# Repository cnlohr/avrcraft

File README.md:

# avrcraft (For Minecraft 1.11)

Minecraft server optimized for 8-bit devices.

Check out the AVR version of this in this video:
http://www.youtube.com/watch?v=EZRLOanNQ_w

This has a few subprojects.
* dumbcraft => Minimalistic Core C Minecraft Server
+ demo_x86_dumbcraft => dumbcraft wrapper for Linux desktops
+ demo_mineandhttp => dumbcraft wrapper for atmega328
* http => http server and demo
* avr_hardware => board layout design for AVR server
* ipcore => core AVR IP stack for the enc424j600 (Though has been ported to a wide variety of targets)
* mfs => minimalistic read-only in-flash filesystem for AVRs
* microsd => minimalistic FAT32 read-only SD/SDHC filesystem for AVRs
* ntsc => Code to help produce text-mode NTSC.

+indicates available tests.

## Installing Minecraft 11.1

Install JDK 8

`sudo apt-get install openjdk-8-jre`

Download the official Minecraft Launcher.

Click "Minecraft: Java Edition"
Click the "Installations" tab.
Create a new installation.
Select Minecraft 1.11 from the list.
Under more settings, select `/usr/lib/jvm/java-8-openjdk-amd64/bin/java`

Launch!

## LICENSE
All code in this repository that was authored by me is freely licensable under the MIT/x11 or NewBSD licenses.

## Original README (For running on 8-bit AVRs)

My 8-bit Microscope Slide Minecraft Server

All contents is Copyright 2012 <>< Charles Lohr
All code and documentation is licensed under the MIT-x11 or NewBSD license.
You choose.  See license info at the end of this readme.
You can use this minecraft server and associated TCP/IP stack commercially.

Check out the AVR version of this in this video:
http://www.youtube.com/watch?v=EZRLOanNQ_w

This has a few subprojects.
* dumbcraft => Minimalistic Core C Minecraft Server
+ demo_x86_dumbcraft => dumbcraft wrapper for Linux desktops
+ demo_mineandhttp => dumbcraft wrapper for atmega328
* http => http server and demo
* avr_hardware => board layout design for AVR server
* ipcore => core AVR IP stack for the enc424j600
* mfs => minimalistic read-only in-flash filesystem for AVRs
* microsd => minimalistic FAT32 read-only SD/SDHC filesystem for AVRs
* ntsc => Code to help produce text-mode NTSC.
+indicates available tests.

----Overview----

This is my 8-bit AVR Minecraft Server... and some extra goodies.  This package
includes:

  * 754lib - A toolset for IEEE754-1985 doubles and floats to fixed point
  * os_generic - My toolset threads (unused), mutices (unused), and timing
  * util10 - My integer->string toolset for this project.
  * dumbcraft (.c, .h)
  * an x86 demo for dumbcraft (compiles and runs on Linux)
  * an AVR-buildable copy (see below)
  * a tool for generating gzipped map chunks (requires Linux)

The AVR folder contains:

  * avr_print - SPI debugging toolset (for use with tinyisp and tinyispterm)
  * my bitbanged ethernet (MAC + ARP + ICMP + UDP + TCP) driver (see below)
  * a really dumb HTTP server
  * a driver for SD cards (and a FAT32 driver) NO SUPPORT FOR FAT16!

Oh yeah, with debugging on, this all fits in about 17kB.

Depending on your settings (dumbcraft circular buffer, etc.) you can use
from about 600 bytes of static RAM to about 1.5 comfortably.

Sadly this does not include the stack, so if you can push data to the
clients and forget about it, that's probably for the best.

----What the dumbcraft does (and doesn't do)----

Dumbcraft is split into a C file for the core, and a user C file that contains
various action-related functions that you must support, i.e.:
  * void InitDumbgame()
  * void DoCustomPreloadStep( uint8_t playerid )
  * void PlayerTickUpdate( int playerid )
  * void PlayerClick( uint8_t playerid, uint8_t x, uint8_t y, uint8_t z )
  * void PlayerUpdate( uint8_t playerid )
  * uint8_t ClientHandleChat( char * chat, uint8_t chatlen )

The .C file contains the core dumbcraft toolset.  Because it doesn't support
any mode of communications with the outside world, all communications must be
done through various functions.  These functions interface 

What works:
  * The stock Minecraft 1.4.2 Server on Windows or Linux (most of the time)
  * More than one player
  * Running around
  * Pulling Levers
  * Updating blocks
  * Loading main map chunk
  * Chat

What doesn't work:
  * Day/night
  * MOBs
  * Physics
  * Animations
  * Crafting
  * Falling Blocks
  * Mining
  * Placing Blocks
  * Collecting things
  * The Nether
  * The End
  * Redstone
  * Water
  * Lava
  * Well, just about everything.

Take a look through dumbcraft.c to get a better hint as to how this all goes together.

----Mapmake----

Map make creates a chunk to be sent by 0x33.  This code doesn't seem to work
very well... It seems to work well enough to make big plot of green ground.

Try dinking with this to figure out why some other chunk types don't work?

It's used to generate the 'mapdata' buffer used in dumbcraft.c

----My IP Stack----

I wrote my own TCP/IP stack for this project, I've been working with it for
quite some time and I needed a good test.  Minecraft has shown to be an
excellent test.  It uses an ENC424j600 from Microchip in SPI mode. It doesn't
use the SPI hardware on an AVR, instead it bit bangs all communications with
it.  This is to make it possible to put it on any geographically convenient
pins.  (I do this on one-layer)

The stack contains the main MAC code and a file for the low level SPI
functionality.  Since the SPI has to be really fast, I've opted to write it
in assembly.

If you want to use the TCP/IP stack, you can feel free to copy it all out,
including test.c and rip out my code.  You'll need the basic callbacks from
TCP or UDP, but other than that you're good to go.

Reconfigure eth_config.h to your situation and profit.  You can get a UDP
server in a little under 4kB, and TCP for an extra ~2.5k more.

I included an HTTP server with it, but it barely counts as an HTTP server
since it requires additional code to serve ... anything.  You can see that it
is difficult to get it to server webpages from the SD card :-/.

----My FAT32/SD SPI Stack----

This stack is still pretty buggy but lets you read files from a FAT32
partition on a SD card.  It can either bin the root or in the FIRST partition.

It can list files in a folder, seek to folders, open files and read them 
sequentially... that's... about... it. 

The SD driver supports SDHC and SD cards and supports reading/writing at the
block level.  Keep in mind the FAT32 driver does not support writing.

Consider the test.c in the avr folder an example of how to do this.

----Building----

You'll need at the minimum: avrdude, avr-gcc and basic build-utils. I
recommend you get my copy of tinyispterm since that'll help you debug.

It prints debugging data through the SPI port if -DMUTE_PRINTF isn't set.
Everything's geared around a TinyISP from LadyAda... I personally use a tiny
variant of it I designed.  You can get the single-layer designs and the tool
here:

https://github.com/cnlohr/tinyispterm

The hardware details for this project can be found in the avr_hardware folder.

I am not a trained electrical engineer.  You will have to know your stuff
before venturing on this project!  It is tricky, and I didn't really document
anything very well.

I designed the PCB in ExpressPCB and designed the schematic later.  They don't
match and I got frustrated, so trust the PCB over the SCH.

Yes, it's a single layer.  No, there are no jumpers.

----Resources and Thanks----

Special thanks to the folks at #mcdevs.  They made this awesome thing here:
http://www.wiki.vg/Protocol

Thanks to nickelpro at #mcdevs for helping me with 1.7 support.

I used a few guides when working on the SD card code.
http://www.esawdust.com/blog/serial/files/SPI_SD_MMC_ATMega128_AVR.html
http://elm-chan.org/docs/mmc/mmc_e.html 

For the FAT32 driver, I used this:
http://staff.washington.edu/dittrich/misc/fatgen103.pdf

----The MIT/x11 License----

Permission is hereby granted, free of charge, to any person obtaining a copy
of this software and associated documentation files (the "Software"), to deal
in the Software without restriction, including without limitation the rights
to use, copy, modify, merge, publish, distribute, sublicense, and/or sell
copies of the Software, and to permit persons to whom the Software is
furnished to do so, subject to the following conditions:

The above copyright notice and this permission notice shall be included in
all copies or substantial portions of the Software.

THE SOFTWARE IS PROVIDED "AS IS", WITHOUT WARRANTY OF ANY KIND, EXPRESS OR
IMPLIED, INCLUDING BUT NOT LIMITED TO THE WARRANTIES OF MERCHANTABILITY,
FITNESS FOR A PARTICULAR PURPOSE AND NONINFRINGEMENT. IN NO EVENT SHALL THE
AUTHORS OR COPYRIGHT HOLDERS BE LIABLE FOR ANY CLAIM, DAMAGES OR OTHER
LIABILITY, WHETHER IN AN ACTION OF CONTRACT, TORT OR OTHERWISE, ARISING FROM,
OUT OF OR IN CONNECTION WITH THE SOFTWARE OR THE USE OR OTHER DEALINGS IN THE
SOFTWARE.

----The NewBSD License----

Redistribution and use in source and binary forms, with or without
modification, are permitted provided that the following conditions are met:

    Redistributions of source code must retain the above copyright notice,
     this list of conditions and the following disclaimer.

    Redistributions in binary form must reproduce the above copyright notice,
     this list of conditions and the following disclaimer in the documentation
     and/or other materials provided with the distribution.

THIS SOFTWARE IS PROVIDED BY THE COPYRIGHT HOLDERS AND CONTRIBUTORS "AS IS"
AND ANY EXPRESS OR IMPLIED WARRANTIES, INCLUDING, BUT NOT LIMITED TO, THE
IMPLIED WARRANTIES OF MERCHANTABILITY AND FITNESS FOR A PARTICULAR PURPOSE
ARE DISCLAIMED. IN NO EVENT SHALL THE COPYRIGHT HOLDER OR CONTRIBUTORS BE
LIABLE FOR ANY DIRECT, INDIRECT, INCIDENTAL, SPECIAL, EXEMPLARY, OR
CONSEQUENTIAL DAMAGES (INCLUDING, BUT NOT LIMITED TO, PROCUREMENT OF
SUBSTITUTE GOODS OR SERVICES; LOSS OF USE, DATA, OR PROFITS; OR BUSINESS
INTERRUPTION) HOWEVER CAUSED AND ON ANY THEORY OF LIABILITY, WHETHER IN
CONTRACT, STRICT LIABILITY, OR TORT (INCLUDING NEGLIGENCE OR OTHERWISE)
ARISING IN ANY WAY OUT OF THE USE OF THIS SOFTWARE, EVEN IF ADVISED OF
THE POSSIBILITY OF SUCH DAMAGE.

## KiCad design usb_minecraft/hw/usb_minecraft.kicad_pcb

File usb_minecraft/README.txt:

THIS SUBPROJECT IS AWFUL.

DO NOT USE IT FOR ANYTHING.

IT IS NOT INTENDED AS A LEGITIMATE SOLUTION AND CRASHES ALL THE TIME.

There's a reason I called my modded TCP stack "tcp_awful."  It actually drops packets!

But, I did it, I shoehorned a full Minecraft server down to under 1k RAM, using a USB RNDIS Ethernet driver from LUFA.

IP is 192.168.55.243:25565... It totally works.

(Minecraft 1.8)

Boy it would be nice to know what's causing most of these errors!!

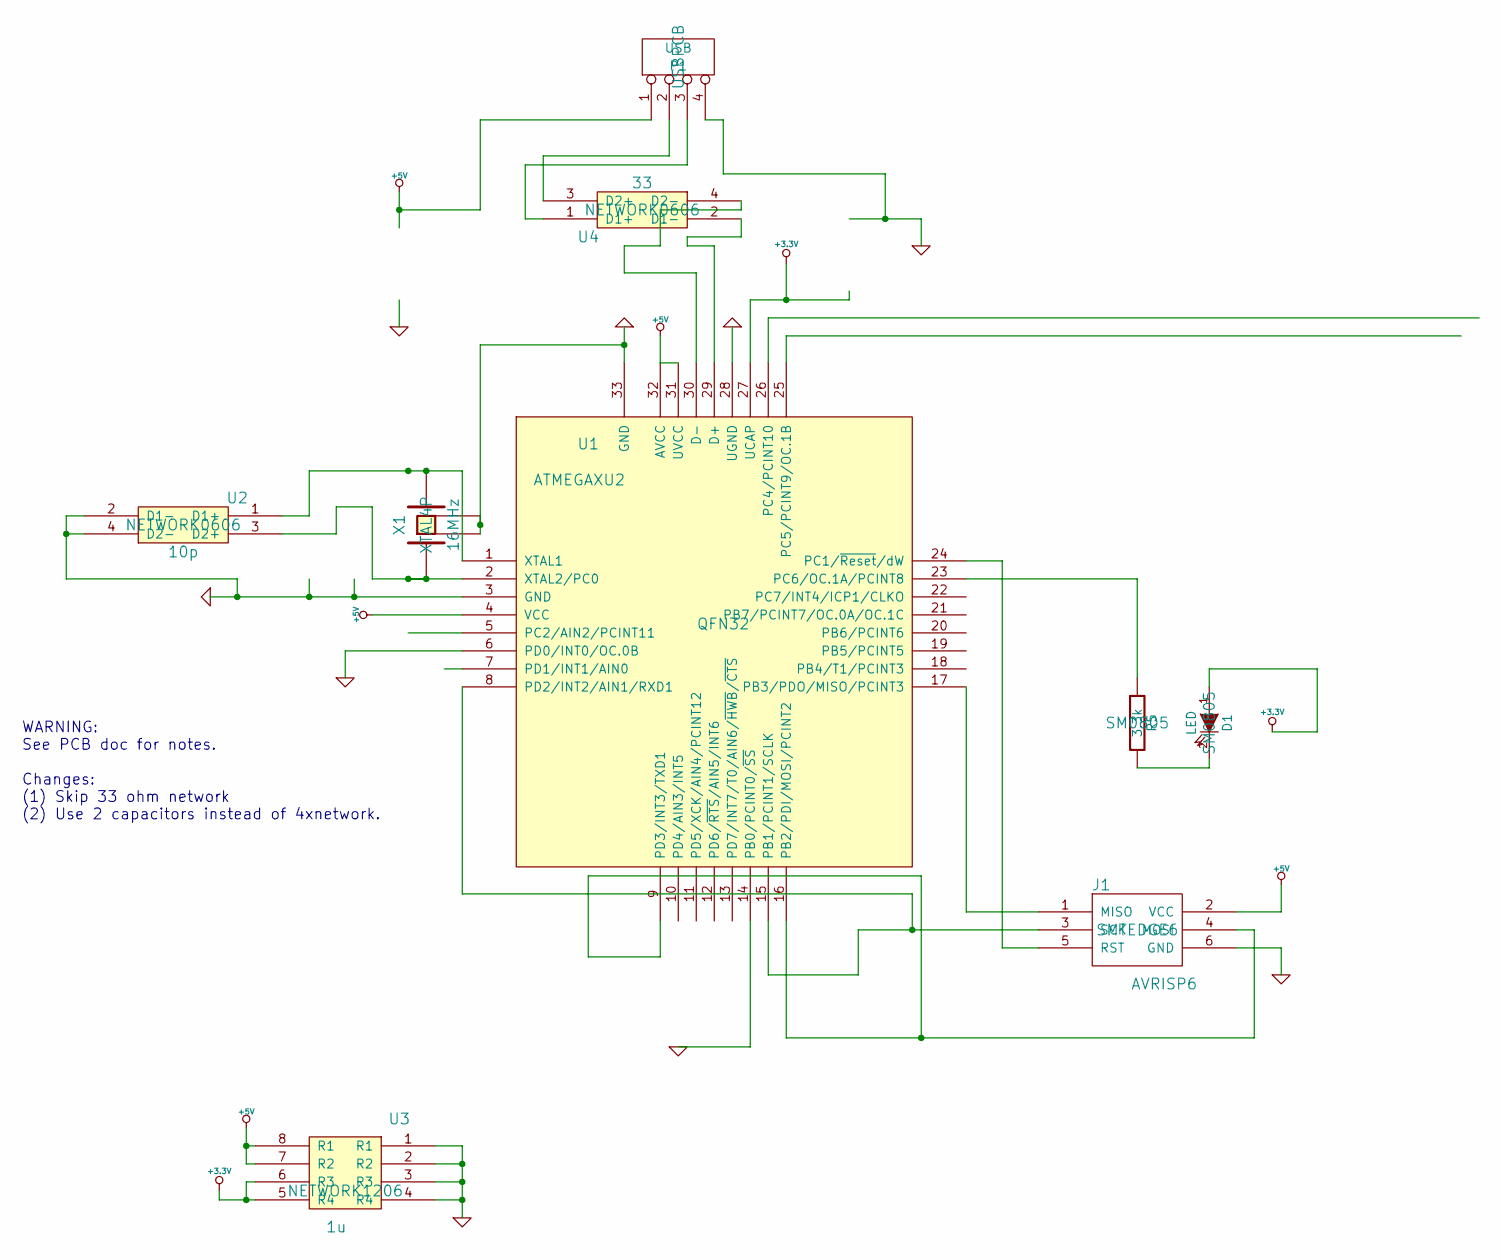
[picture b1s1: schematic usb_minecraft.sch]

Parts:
D1: LED; SM0805
J1: AVRISP6; SMTEDGE6
P1: USB; USBPCB
R5: 3.3k; SM0805
U1: ATMEGAXU2; QFN32
U2: 10p; NETWORK0606
U3: 1u; NETWORK1206
U4: 33; NETWORK0606
X1: 16MHz; XTAL4P

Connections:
+3.3V: D1.1 (A), U1.27 (UCAP), U3.5 (R4), U3.6 (R3)
+5V: J1.2 (VCC), P1.1, U1.4 (VCC), U1.31 (UVCC), U1.32 (AVCC), U3.7 (R2), U3.8 (R1)
GND: J1.6 (GND), P1.4, U1.3 (GND), U1.6 (PD0/INT0/OC.0B), U1.14 (PB0/PCINT0/~SS), U1.28 (UGND), U1.33 (GND), U2.2 (D1-), U2.4 (D2-), U3.1 (R1), U3.2 (R2), U3.3 (R3), U3.4 (R4), X1.3 (GND), X1.4 (GND)
unnamed: U1.29 (D+), U4.2 (D1-)
unnamed: U1.30 (D-), U4.4 (D2-)
unnamed: R5.1, U1.23 (PC6/OC.1A/PCINT8)
unnamed: J1.4 (MOSI), U1.9 (PD3/INT3/TXD1), U1.16 (PB2/PDI/MOSI/PCINT2)
unnamed: D1.2 (K), R5.2
unnamed: P1.2, U4.3 (D2+)
unnamed: P1.3, U4.1 (D1+)
unnamed: J1.3 (SCK), U1.8 (PD2/INT2/AIN1/RXD1), U1.15 (PB1/PCINT1/SCLK)
unnamed: J1.5 (RST), U1.24 (PC1/~Reset~/dW)
unnamed: J1.1 (MISO), U1.17 (PB3/PDO/MISO/PCINT3)
unnamed: U1.2 (XTAL2/PC0), U2.3 (D2+), X1.1
unnamed: U1.1 (XTAL1), U2.1 (D1+), X1.2

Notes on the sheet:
WARNING: See PCB doc for notes. Changes: (1) Skip 33 ohm network (2) Use 2 capacitors instead of 4xnetwork.

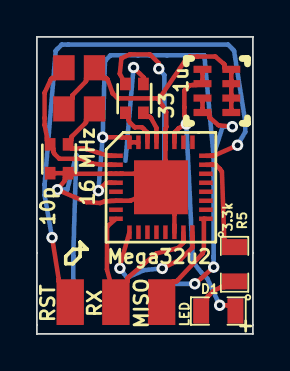
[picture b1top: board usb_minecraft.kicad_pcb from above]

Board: 2 copper layers, 12.0 x 16.5 mm, 9 parts (1 on the bottom side), 15 nets.

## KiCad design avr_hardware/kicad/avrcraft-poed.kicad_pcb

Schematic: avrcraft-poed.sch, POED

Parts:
C1: NP; SM0603
C4, C8: 10u; SM0805
C9: 100u; SM1206; Voltage 6.3v; Digikey 490-7217-1-ND
C12: .22u; SM0603
C13: .01u; SM0603
C15: 100u; PanasonicD8Cap
C16: 10u; SM0603
CN1, CN3: 10p; NETWORK0606
CN2, CN5: .1u; NETWORK0606
CN4: 10n; NETWORK1206
D1: 5050RGB
D3, D4: MB2S-TP; BESOP-4
D5: DIODESCH; DO_214AA
D7: ZENER-5.6V/2W; DO_214AA
H1, H2, H3, H4: ?; 632HOLE
J1: AVRISP6; RIBBON6SMT
L1: 68uH; BOURNS-SRR1280
P1: ETHERNET; SMT_ETHERNET
P2: ADC0; .1SMTPIN
P3: ADC1; .1SMTPIN
P4, P10: GND; .1SMTPIN
P5: 6MULTI; RIBBON6SMT
P6: 5V; .1SMTPIN
P7: 3V3; .1SMTPIN
P8: CONN_3X2; RIBBON6SMT
P9: 48V; .1SMTPIN
P11: +5V; .2SMTPIN
P12, P13: GND; .2SMTPIN
P14: +3.3V; .2SMTPIN
P15: POE+; .2SMTPIN
R1: 10; SM0805
R3: 12.4k; SM0603
R9, R11: 25k; SM0603
R13: 1k; SM0603
R15: 270k; SM0805
R16: NC; SM0805
RN1, RN4: 4.7k; NETWORK0606
RN2: 1k; NETWORK1206
RN3: 49.9; NETWORK1206
T1: S558-5999-T7-F; BELFuse-S553
U1: ATMEGA328; TQFP32
U2: MCP1824v3.3; SOT23-5
U3: ENC424J600; TQFP44
U4: A4447SLJTR; SO8E-WITHPAD
U5: S4SRP; DO-214AA
X1: 20MHz; XTAL4P
X2: 25MHz; XTAL4P

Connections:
+3.3V: C8.1, CN5.2, P5.4, P7.1, P14.1, R1.1, RN1.1, RN1.3, RN2.4, U2.5 (OUT), U3.4 (VDDosc), U3.12 (VDDpll), U3.15 (VDDrx), U3.18 (VDDtx), U3.44 (VDD)
+5V: C1.1, C9.1, C16.1, CN2.2, CN5.4, J1.2 (VCC), L1.1, P5.2, P6.1, P8.2, P11.1, RN4.2, U1.4 (VCC), U1.6 (VCC), U1.18 (AVCC), U2.1 (Vin), U2.3 (~SHDN), U4.6 (VIBAS)
/HighCOut: C13.1, D5.2 (K), L1.2, U4.7 (LXOUT)
/MISO: J1.1 (MISO), U1.16 ((PCINT4/MISO)PB4)
/MOSI: J1.4 (MOSI), U1.15 ((PCINT3/OC2A/MOSI)PB3), U1.19 (ADC6)
/PB0/CLKO: P8.1, U1.12 ((PCINT0/CLKO/ICP1)PB0)
/PB1/OC1A: P5.5, U1.13 ((PCINT1/OC1A)PB1)
/PD2/INT0: P8.3, U1.32 ((PCINT18/INT0)PD2)
/PD3/INT1/OC2B: P8.4, U1.1 ((PCINT19/OC2B/INT1)PD3)
/PD5/OC0B: P8.5, U1.9 ((PCINT21/OC0B/T1)PD5)
/POE+: D3.3 (+), D4.3 (+), D7.2 (K)
/POE+A: C12.2, C15.2, P9.1, P15.1, R16.2, U4.8 (VIN), U5.1
/POE+C: D7.1 (A), R15.1, U5.3
/POEA: D3.2 (AC), P1.7, P1.8, R11.1
/POEB: D3.1 (AC), P1.4, P1.5, R11.2
/POEC: D4.2 (AC), R9.2, T1.2 (PM)
/POED: D4.1 (AC), R9.1, T1.7 (PM)
/RST: J1.5 (RST), U1.29 ((PCINT14/RESET)PC6)
/SCK: J1.3 (SCK), U1.17 ((PCINT5/SCK)PB5), U1.22 (ADC7)
/SCL/PC5/PD7: P5.3, RN1.2, U1.11 ((PCINT23/AIN1)PD7), U1.28 ((PCINT14/SCL/ADC5)PC5)
/SDA/PC4/OC0A: P5.1, RN1.4, U1.10 ((PCINT22/OC0A/AIN0)PD6), U1.27 ((PCINT12/SDA/ADC4)PC4)
BLUE: RN2.3, U1.25 ((PCINT10/ADC2)PC2)
GND: C4.1, C8.2, C9.2, C12.1, C15.1, C16.2, CN1.1, CN1.3, CN2.1, CN2.3, CN3.2, CN3.4, CN4.3, CN4.4, CN5.1, CN5.3, D1.4, D1.5, D1.6, D3.4 (-), D4.4 (-), D5.1 (A), J1.6 (GND), P1.9, P1.10, P4.1, P5.6, P8.6, P10.1, P12.1, P13.1, R3.2, R13.2, RN4.3, U1.3 (GND), U1.5 (GND), U1.14 ((PCINT2/OC1B/SS)PB2), U1.21 (GND), U2.2 (GND), U3.1 (VSSosc), U3.13 (VSSpll), U3.14 (VSSrx), U3.19 (VSSrx), U3.22 (VSStx), U3.33 (VSS), U3.42 (VSS), U4.2 (ENB), U4.4 (GND), U4.9 (PAD), X1.3 (GND), X1.4 (GND), X2.3 (GND), X2.4 (GND)
unnamed: C13.2, U4.1 (BOOT)
unnamed: P3.1, U1.24 ((PCINT9/ADC1)PC1)
unnamed: CN4.5, R1.2, RN3.3, RN3.4, T1.15
unnamed: CN4.2, T1.9 (S1)
unnamed: C1.2, R13.1, RN4.1, U4.5 (FDBK)
unnamed: P1.2, T1.1 (RX1)
unnamed: R15.2, R16.1, U5.2
unnamed: C4.2, U3.43 (Vcap)
unnamed: CN1.4, U1.8 ((PCINT7/XTAL2/TOSC2)PB7), X1.2
unnamed: RN2.2, U3.9 (LEDB)
unnamed: CN1.2, U1.7 ((PCINT6/XTAL1/TOSC1)PB6), X1.1
unnamed: RN2.1, U3.10 (LEDA)
unnamed: R3.1, U3.11 (RBIAS)
unnamed: CN2.4, U1.20 (AREF)
unnamed: U1.2 ((PCINT20/XCK/T0)PD4), U3.37 (SCK/AL)
unnamed: RN3.5, T1.16 (S2), U3.21 (TPOUT-)
unnamed: U1.31 ((PCINT17/TXD)PD1), U3.36 (SI/RD/R~W~)
unnamed: U1.30 ((PCINT16/RXD)PD0), U3.35 (SO/WR/EN)
unnamed: U1.26 ((PCINT11/ADC3)PC3), U3.34 (~CS~/CS)
unnamed: P2.1, U1.23 ((PCINT8/ADC0)PC0)
unnamed: CN4.1, T1.11 (S2)
unnamed: D1.3, RN2.6
unnamed: D1.2, RN2.7
unnamed: D1.1, RN2.8
unnamed: CN4.6, RN3.1, RN3.2, T1.10 (4)
unnamed: RN3.6, T1.14 (S1), U3.20 (TPOUT+)
unnamed: CN4.8, RN3.8, U3.16 (TPIN+)
unnamed: CN4.7, RN3.7, U3.17 (TPIN-)
unnamed: P1.3, T1.6 (PR1)
unnamed: RN2.5, U3.24 (~INT~/SPISEL)
unnamed: CN3.1, U3.3 (OSC1), X2.1
unnamed: CN3.3, U3.2 (OSC2), X2.2
unnamed: P1.6, T1.8 (PR2)
unnamed: RN4.4, U4.3 (TSET)
unnamed: P1.1, T1.3 (PR2)

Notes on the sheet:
NOTE: D7 may be replaced by 0 Ohm If >52V operation is not required.
Connect if you want interrupt support
NOTE: Diode D5 is a little bigger than 0805
NOTE: 5v Rail should be roughly 4.5V
TP+
TP-
49CT
10-Ohm-3V3

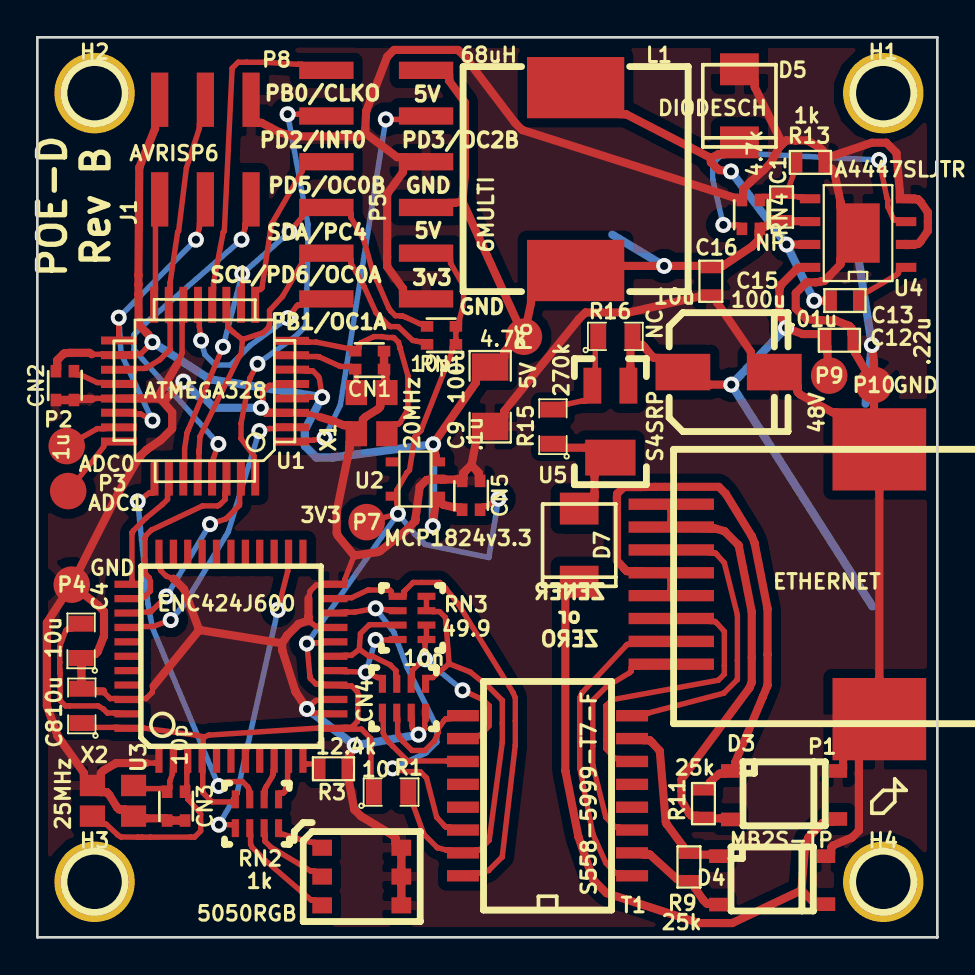
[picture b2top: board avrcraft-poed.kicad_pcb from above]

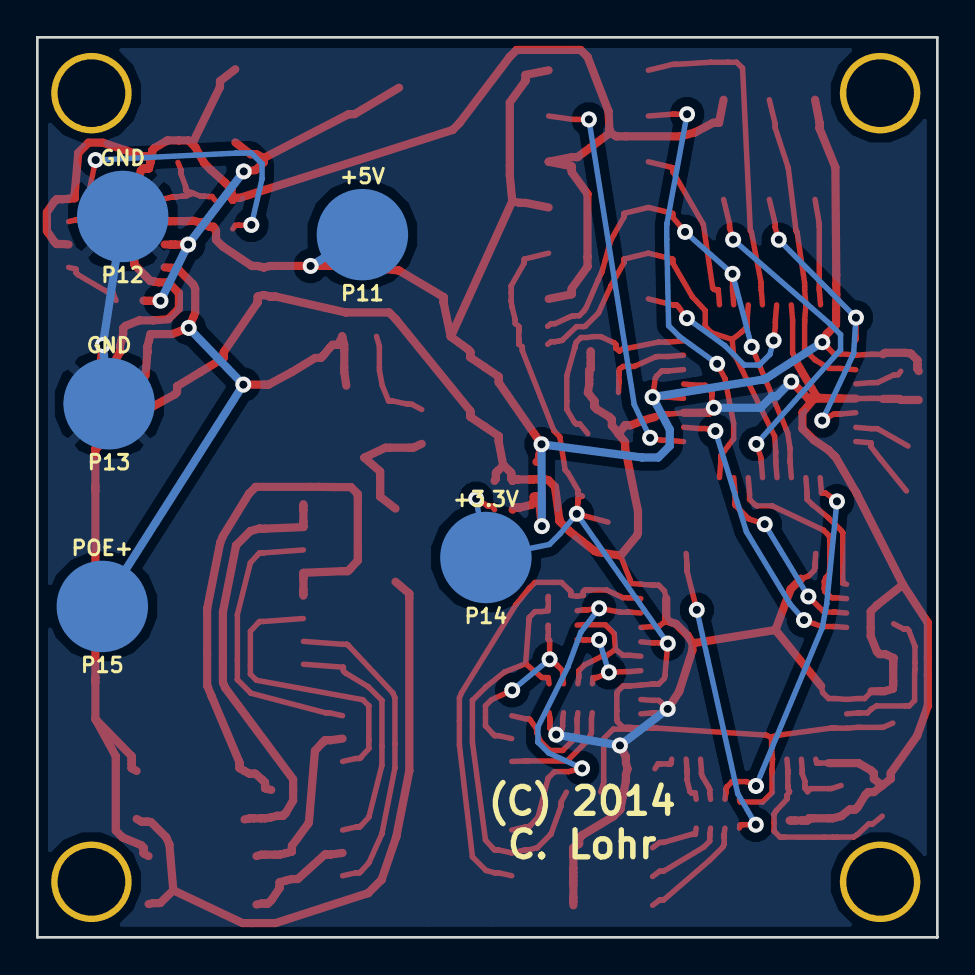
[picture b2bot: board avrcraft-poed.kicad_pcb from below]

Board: 2 copper layers, 50.0 x 50.0 mm, 58 parts (5 on the bottom side), 58 nets.

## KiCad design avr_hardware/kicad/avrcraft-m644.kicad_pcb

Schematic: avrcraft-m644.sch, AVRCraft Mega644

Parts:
C1, C5, C17: 1u; SM0603
C2, C3, C10, C11: 12p; SM0603
C4, C6, C8: 10u; SM0805
C9: 100u; SM1206; Voltage 6.3v
D1: 5050RGB
D3: DIODE; SM1206
IC1: ATMEGA1284P-A; TQFP44
J1: AVRISP6; RIBBON6SMT
P1: ETHERNET; SMT_ETHERNET
P2: PWM; RIBBON6SMT
P3: I2C; RIBBON6SMT
P4: GND; .1SMTPIN
P5: SERIAL; RIBBON6SMT
P6: DIO; PHOENIX1935187
P7: 3V3; .1SMTPIN
P8, P9: AIO; PHOENIX1935187
P10, P14: PWR; PHOENIX1935187
P11: +5V; .1SMTPIN
P12, P13, P15, P16: GND; 632HOLE
R1, R2: FB; SM0805
R3: 12.4k; SM0603
R10: 10; SM0805
T1: S558-5999-T7-F; BELFuse-S553
U1, U4: RN-150; 1206NETWORK
U2: MCP1824v3.3; SOT23-5
U3: ENC424J600; QFN44
U5, U8: RN-1k; 1206NETWORK
U6: CN-10n; 1206NETWORK
U7: RN-49.9; 1206NETWORK
U9: AP1117v5.0; SOT223
U10: LSM303C; 12LGA
U11: CN-100n; 1206NETWORK
X1: 20MHz; XTAL4P
X2: 25MHz; XTAL4P

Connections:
+3.3V: C8.1, D1.1, P3.4, P7.1, R2.2, R10.1, U2.5 (OUT), U3.4 (VDDosc), U3.12 (VDDpll), U3.15 (VDDrx), U3.18 (VDDtx), U3.44 (VDD), U5.8, U8.7, U8.8, U10.2, U10.3, U10.10, U11.1
+5V: C9.1, C17.1, IC1.5, IC1.17, IC1.38, J1.2 (VCC), P3.2, P5.2, P10.1, P10.2, P11.1, R1.1, U2.1 (Vin), U2.3 (~SHDN), U9.2, U9.4, U11.2
+12V: D3.2, P2.2, U9.3
/SCL: IC1.19, P3.3, U8.2, U10.1
/SDA: IC1.20, P3.1, U8.1, U10.4
GND: C1.2, C2.1, C3.1, C4.1, C5.2, C6.1, C8.2, C9.2, C10.2, C11.2, C17.2, IC1.6, IC1.18, IC1.28, IC1.39, IC1.44, J1.6 (GND), P1.9, P1.10, P2.6, P3.6, P4.1, P5.6, P6.1, P10.3, P10.4, P12.1, P13.1, P14.3, P14.4, P15.1, P16.1, R3.2, U2.2 (GND), U3.1 (VSSosc), U3.13 (VSSpll), U3.14 (VSSrx), U3.19 (VSSrx), U3.22 (VSStx), U3.33 (VSS), U3.42 (VSS), U5.5, U5.6, U5.7, U6.3, U6.4, U9.1, U10.6, U10.8, U11.5, U11.6, U11.7, U11.8, X1.3 (GND), X1.4 (GND), X2.3 (GND), X2.4 (GND)
unnamed: IC1.26, U3.34 (~CS~/CS)
unnamed: IC1.43, P2.4
unnamed: IC1.14, P2.5
unnamed: IC1.15, P2.3
unnamed: P1.6, T1.8 (PR2)
unnamed: U3.16 (TPIN+), U6.1, U7.8
unnamed: T1.10 (4), U6.6, U7.1, U7.2
unnamed: P8.4, U1.8
unnamed: P8.3, U1.7
unnamed: P8.2, U1.6
unnamed: P8.1, U1.5
unnamed: P9.4, U4.8
unnamed: P9.3, U4.7
unnamed: P9.2, U4.6
unnamed: P9.1, U4.5
unnamed: IC1.37, U1.1
unnamed: IC1.36, U1.2
unnamed: IC1.35, U1.3
unnamed: IC1.34, U1.4
unnamed: IC1.33, U4.1
unnamed: IC1.16, P2.1
unnamed: IC1.3, J1.3 (SCK)
unnamed: IC1.2, J1.1 (MISO)
unnamed: IC1.9, P5.1
unnamed: D1.3, U3.10 (LEDA)
unnamed: D1.2, U3.9 (LEDB)
unnamed: IC1.40, P5.3
unnamed: IC1.24, P6.4
unnamed: IC1.23, P6.3
unnamed: IC1.22, P6.2
unnamed: D3.1, P14.1, P14.2
unnamed: IC1.41, P5.5
unnamed: IC1.10, P5.4
unnamed: D1.4, U5.4
unnamed: D1.5, U5.3
unnamed: D1.6, U5.2
unnamed: R10.2, T1.15, U6.5, U7.3, U7.4
unnamed: T1.9 (S1), U6.7
unnamed: T1.11 (S2), U6.8
unnamed: P1.2, T1.1 (RX1)
unnamed: P1.1, T1.3 (PR2)
unnamed: T1.16 (S2), U3.21 (TPOUT-), U7.5
unnamed: R3.1, U3.11 (RBIAS)
unnamed: C4.2, U3.43 (Vcap)
unnamed: P1.7, P1.8
unnamed: P1.4, P1.5
unnamed: P1.3, T1.6 (PR1)
unnamed: T1.14 (S1), U3.20 (TPOUT+), U7.6
unnamed: U3.17 (TPIN-), U6.2, U7.7
unnamed: IC1.13, U3.37 (SCK/AL)
unnamed: IC1.12, U3.36 (SI/RD/R~W~)
unnamed: IC1.11, U3.35 (SO/WR/EN)
unnamed: IC1.1, J1.4 (MOSI)
unnamed: IC1.32, U4.2
unnamed: IC1.31, U4.3
unnamed: IC1.30, U4.4
unnamed: C1.1, IC1.29
unnamed: IC1.25, U3.24 (~INT~/SPISEL), U5.1
unnamed: IC1.4, J1.5 (RST)
unnamed: C5.1, IC1.27, R1.2
unnamed: C2.2, IC1.8, X1.1
unnamed: C3.2, IC1.7, X1.2
unnamed: IC1.21, P3.5
unnamed: C11.1, U3.3 (OSC1), X2.2
unnamed: C10.1, U3.2 (OSC2), X2.1
unnamed: U10.5, U11.4
unnamed: C6.2, R2.1, U10.9, U11.3

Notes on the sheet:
NOTE: Diode D5 is a little bigger than 0805

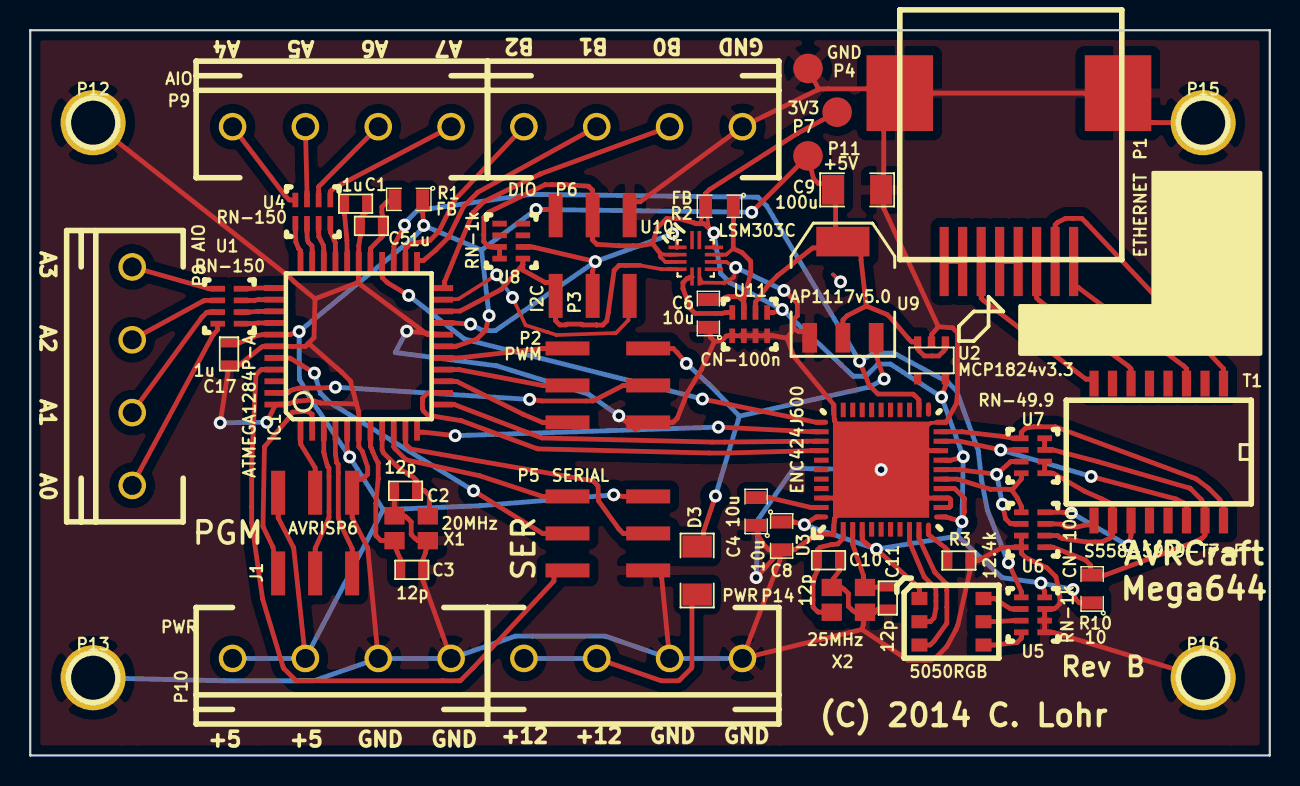
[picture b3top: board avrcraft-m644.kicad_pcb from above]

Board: 2 copper layers, 85.1 x 49.8 mm, 49 parts (0 on the bottom side), 73 nets.

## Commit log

2012-11-16 initial commit!
2012-11-16 remove extra file here
2012-11-16 update the bom
2012-11-17 move arp address to target into the TCP sets.
2012-11-18 update changes - fix tcp not retransmitting
2012-11-18 change re-transmit functionality, now stripped down to minimal functionality. Seems faster, smaller and more reliable.
2012-11-18 update comments on TCP-related things
2012-11-18 move http code into http area to make more sense... bang a few other things out.
2012-11-18 fix strange sending in phantom length value
2012-11-18 Switch way Makefile does it's program.map generation. Overhaul HTTP server. Add new mechanism for reading FAT sector-at-a-time Greatly improve MicroSD performance.
    Off the SD card with multiple connections, performance goes up to ~120kB/sec
2012-11-28 major re-architecture
2012-11-28 move the game to where it should go
2012-11-28 oops forgot to commit these changes
2012-11-28 move the map making tools to the proper plac
2012-11-28 update http demos, etc.
2012-11-28 add the http eth_config thing + use the DMA engine for copying.
    This greatly reduces stack consumption!
2012-11-28 fix up ping code, add note about DMA copying, tweak Minecraft demo server
2012-11-28 move dumbcraft back to a 512-byte extra buffer
2012-11-28 move the x86 demo over to its own place
2012-11-29 Update TCP stack - remove extra 4-bytes per connection, and clean up usage (saves us about 120 bytes of flash)
2012-11-30 wholesale updates
    Forgot to commit these from last night.
2012-11-30 cleanup: use blanket function to /format/ the http connection
2012-12-01 add fonter
2012-12-01 fix up http and use new NTSC output mechanism
2012-12-19 update for g35
2012-12-19 use 20 MHz now
2013-01-25 Add the avrcraft kicad project files
2013-01-29 yay added newer design
2013-01-31 updated designs to reflect findings
2013-02-03 update files for actual hardware
2013-02-03 oops forgot to commit this.
2013-02-03 update overall design!
2013-02-03 move files back to where the yneed to be
2013-02-04 fix naming convention
2013-02-04 update with newest board
2013-02-04 update design with POE AND update with all client-side ping support
2013-02-04 update with new code for client IP.
2013-02-04 add the cache for other people's benefit
2013-02-08 update with the microsd stuff
2013-02-08 update the http toolset for use with a memory FS
2013-02-08 update the caches
2013-02-08 don't mute the ping.
2013-02-08 add mfs
2013-02-08 update the video
2013-02-13 update nwe project files :)
2013-02-14 update all the boards ! yay.
2013-02-15 clean up comments in iparpetc and improve high-speed mode
2013-02-16 more awesome HTTP server.
2013-04-11 update timing for fixing clock quanta
2013-04-11 Remove spurious debugging from HTTP
2013-04-11 here's a terminal
2013-04-23 update with more readme information
2013-06-01 update all fot stuff
2013-06-01 update terminal
2013-06-01 add some things
2013-07-04 switch up versions to 1.5.2
2013-07-04 fix chat
2013-08-01 stuff changed.
2013-08-01 update moving some of the labels
2013-08-06 Fix some bugs and stuff, the UDP broadcaster still appaers to be broken, unknown reason.
2013-08-07 move a LOT around and fix the system broadcasting.
    DHCP stil ldoesn't work.
2013-08-09 Update for DHCP
2013-08-10 stuff
2013-08-15 updated hardware
2013-08-16 fix mapping mechanisms.
2013-10-26 Major change: work on FIN packets, plus support for 1.7.2
2013-10-26 switch over to internal pages
2013-11-19 update POE
2013-11-28 few tweaks
2013-12-31 updates!
2013-12-31 change to different EIDs, etc. to make the player updates work on the new systems.
2014-02-10 update poc
2014-02-13 tweak board, ready for printing
2014-02-19 fix for including MAC. For compatibility's sake, we will not use the insert-mac feature of the ENC424j600
2014-04-18 update POEC
2014-04-18 add plots
2014-04-29 update - make build for MIPS possible
2014-04-29 fix warnings, update for version
2014-04-29 add missing unstd reference.
2014-05-03 Disable TXMAC, this causes compatibility issues with other MACs
2014-05-03 Stage a number of optimizations
2014-05-03 further tweaks - make compatible with x86 again.
2014-05-03 remove g35
2014-05-14 fix values
2014-05-30 update: fix the IP stack to be able to handle "lease time" only DHCP packets. Also, update a variable in the schematico
2014-06-11 update DHCP mechanism
2014-06-12 Update: Switch to scratchpads, update TCP to include doublesend option. Allow for smarter TCP handling, and add the option to do further debugging on the enc424j600.
2014-07-11 update with the new design for the m644 board
2014-07-18 add POED stuff (Rough draft)
2014-07-19 update POED for manufacture
2014-07-28 add feature for hardware SPI, plus add code for default lease times
2014-08-09 Update for use with dedicated serial port.
2014-08-09 forgot to remove old (dead) code
2014-08-09 name server properly
2014-09-01 fix: read out local/remote port.
2014-09-01 Oops!! That was really wrong. Trns out this is already sent.
2014-09-06 major change to 1.8
2014-09-06 changes to 1.8
2014-09-06 oops using wrong default data.
2014-09-06 fix stuff for lookat
    WARNING: can't warp right now. I wonder if taht's bad.
2014-09-09 changes - update with new design for LED
2014-09-09 fix for AVR + Add extra util10 + add support for the 32u2
2014-10-24 fix ipcore - check full address
2014-10-24 add the design (or at least a start)
2014-10-25 Check out this awful thing I made. I'll be getting the boards soon to test with, but it looks like you can use RNDIS to run Minecraft. YUCKo
2014-11-27 Yay updates
2017-04-06 Update dumbcraft, getting close to modern Minecraft 1.11.2 support.
2017-04-06 Fix dumbcraft for use with modern clients (1.11.2)
2017-04-06 Fix interface for multiplayer.
2018-12-17 Major progress to the land of 1.13.2 support.
2018-12-17 Add note about where to go with sblockinternal
2020-08-11 Add to readme
2020-08-11 Make dumbcraft work on the 8266.
2020-08-11 fix a crash
2020-08-12 Fix warnings
2020-08-14 Fix disconnect mess on ESP8266.
2020-08-29 Taking a look at 1.16
2020-08-30 Working with 1.15.2
2020-08-30 Ok, functional game with 1.15.2
2020-08-30 HOORAY Speedy and big chunkin time.
2020-08-30 Ok, I think we're good here.
2021-04-23 General cleanup + notes and comments for other block types.
2021-04-27 First stab at 1.16.5. Not quite there.

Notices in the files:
avr_hardware/kicad/avrcraft-m644.kicad_pcb:
(C) 2014 C. Lohr
